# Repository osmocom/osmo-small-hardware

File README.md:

osmo-small-hardware - Various small Osmocom Hardware Projects
=============================================================

This repository contains a number of OSHW (open source hardware)
designs.  They are part of the [Osmocom](https://osmocom.org/) Open
Source Mobile Communications project.

Most of the designs are done in EAGLE CAD; the schematics and board
design files as well as the BOM are contained in this repository.

GIT Repository
--------------

You can clone from the official osmo-small-hardware repository using

	git clone https://gitea.osmocom.org/electronics/osmo-small-hardware

There is a web interface at <https://gitea.osmocom.org/electronics/osmo-small-hardware>

Contributing
------------

Our coding standards are described at
https://osmocom.org/projects/cellular-infrastructure/wiki/Coding_standards

We us a gerrit based patch submission/review process for managing
contributions.  Please see
https://osmocom.org/projects/cellular-infrastructure/wiki/Gerrit for
more details

clock-converter
---------------

The osmo-clock-conv is a small board for low-jitter conversion of a sine
clock into a square clock, based around the LTC6957-4.

* [Homapege](https://osmocom.org/projects/osmo-clock-conv)

clock-generator
---------------

Osmocom Clock Generator board, using the Si5351C clock synthesizer to
derive up to 8 different clocks from a single clock reference, such as a
10MHz GPS-DO or OCXO.

* [Homepage](https://osmocom.org/projects/osmo-clock-gen)

dus-lmt-breakout
----------------

This is a break-out board for the LMT port of Ericsson DUS-31/41
baseband units.

e1-tap
------

The Osmocom E1/T1 tap adapter allows you to tap into the communication
of an E1/T1 line.

* [Homepage](https://osmocom.org/projects/e1-tap)

eksos-rj45-breakout
-------------------

This contains a couple of break-out boards which can be used to break out the
ISDN / PSTN ports of a Nokia EKSOS V5 access network.

gtm900-breakout
---------------

Break-out board for the GTM900B Calypso based GSM cellular modem.

mpcie-breakout
--------------

This is a small break-out board for miniPCIe (mPCIe) type cellular /
WWAN modems.

* [Homepage](https://osmocom.org/projects/mpcie-breakout)

multivoltage-uart
-----------------

* [Homepage](https://osmocom.org/projects/mv-uart)

ngff-breakout
-------------

This is a small break-out board for M.2 (NGFF) type cellular / WWAN
modems.

* [Homepage](https://osmocom.org/projects/ngff-breakout)

ohm4-ocxo
---------

osmo-lea6t-gps
--------------

Small evaluation board for the u-blox LEA6-T timing GPS receiver.

osmo-nvs-gps
------------

Small evaluation board for the NVS GPS receiver.

rj45-jumper-box
---------------

A jumper box for RJ45 cables. Useful for the many different RS232
console pin-outs on RJ45.

* [Homepage](https://osmocom.org/projects/misc-hardware/wiki/RJ45_jumper_box)

rj45-switch
-----------

sc14dect-breakout
-----------------

Small evaluation board for the SC15 DECT module

sfp-breakout + sfp-experimenter
-------------------------------

Boards for playing with SFP transceivers

* [Homepage](https://osmocom.org/projects/misc-hardware/wiki/Sfp-breakout)

siu-clock-breakout
------------------

A break-out board for the clock/sync port on the Ericsson SIU-02

rbs6k-diy-rack
--------------

A DYI small rack for housing Ericsson RBS 6000 equipment like DUL + DUG + RUS made from wooden panels and a laser-cut back plate for fans.

fcd155-breakout
---------------

This is a small break-out board to adapt the RAD FCD-155 8xE1 high-density 44-pin D-SUB connector to 8xRJ45 in standard E1 pinout.

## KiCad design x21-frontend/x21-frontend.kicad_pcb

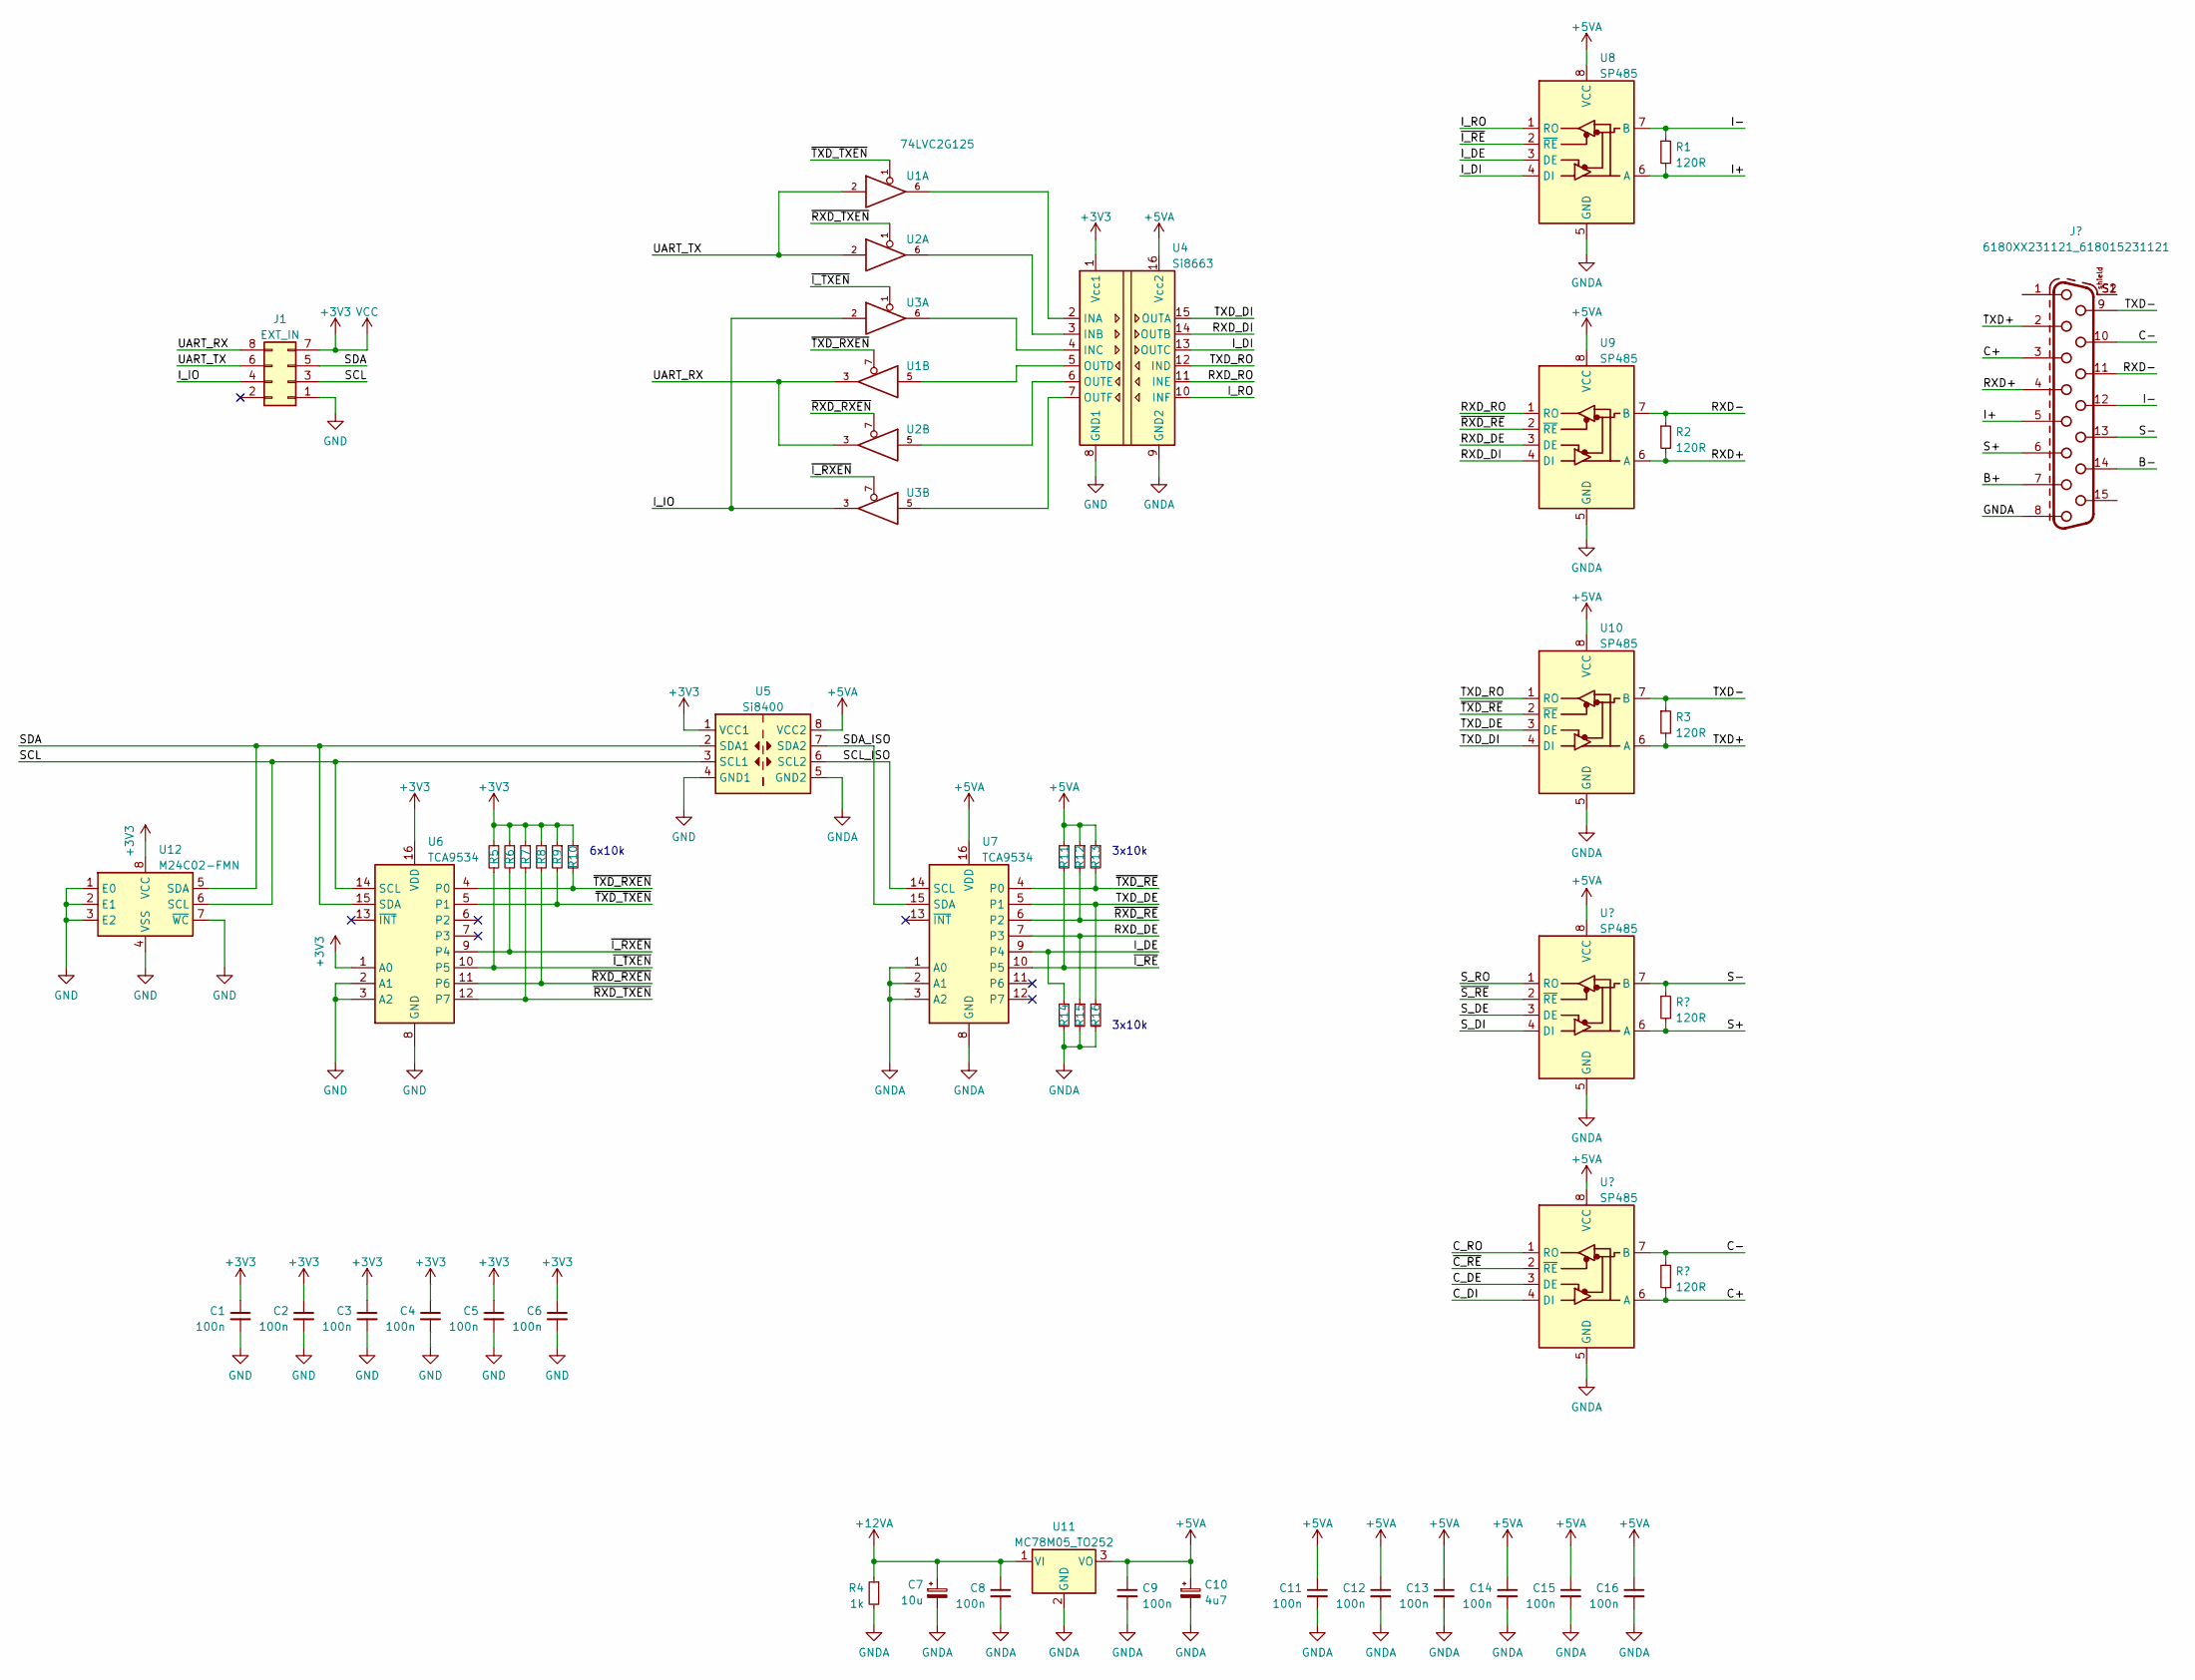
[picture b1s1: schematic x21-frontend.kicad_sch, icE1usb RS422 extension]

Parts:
C1, C2, C3, C4, C5, C6, C8, C9, C11, C12, C13, C14, C15, C16: 100n; C_0603_1608Metric
C7: 10u; CP_EIA-3216-18_Kemet-A
C10: 4u7; CP_EIA-3216-18_Kemet-A
J1: EXT_IN; PinSocket_2x04_P2.54mm_Vertical
R1, R2, R3: 120R; R_0603_1608Metric
R4: 1k; R_0603_1608Metric
R5, R6, R7, R8, R9, R10, R11, R12, R13, R14, R15, R16: 10k; R_0603_1608Metric
U1, U2, U3: 74LVC2G125; TSSOP-8_3x3mm_P0.65mm
U4: Si8663; SSOP-16_3.9x4.9mm_P0.635mm
U5: Si8400; SOIC-8_3.9x4.9mm_P1.27mm
U6, U7: TCA9534; SOIC-16W_7.5x10.3mm_P1.27mm
U8, U9, U10: SP485; SOIC-8_3.9x4.9mm_P1.27mm
U11: MC78M05_TO252; TO-252-2
U12: M24C02-FMN; SOIC-8_3.9x4.9mm_P1.27mm

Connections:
+3V3: C1.1, C2.1, C3.1, C4.1, C5.1, C6.1, J1.7, R5.1, R6.1, R7.1, R8.1, R9.1, R10.1, U1.8 (VCC), U2.8 (VCC), U3.8 (VCC), U4.1 (Vcc1), U5.1 (VCC1), U6.1 (A0), U6.16 (VDD), U12.8 (VCC)
+5VA: C9.1, C10.1, C11.1, C12.1, C13.1, C14.1, C15.1, C16.1, R11.1, R12.1, R13.1, U4.16 (Vcc2), U5.8 (VCC2), U7.16 (VDD), U8.8 (VCC), U9.8 (VCC), U10.8 (VCC), U11.3 (VO)
+12VA: C7.1, C8.1, R4.1, U11.1 (VI); also elsewhere on the board
/PPS+: R1.2, U8.6 (A); also elsewhere on the board
/PPS-: R1.1, U8.7 (B); also elsewhere on the board
/PPS_DE: R14.1, U7.9 (P4), U8.3 (DE)
/PPS_DI: U4.13 (OUTC), U8.4 (DI)
/PPS_IO: J1.4, U3.2, U3.3
/PPS_RO: U4.10 (INF), U8.1 (RO)
/RXD+: R2.2, U9.6 (A); also elsewhere on the board
/RXD-: R2.1, U9.7 (B); also elsewhere on the board
/RXD_DE: R15.1, U7.7 (P3), U9.3 (DE)
/RXD_DI: U4.14 (OUTB), U9.4 (DI)
/RXD_RO: U4.11 (INE), U9.1 (RO)
/SCL: J1.3, U5.3 (SCL1), U6.14 (SCL), U12.6 (SCL)
/SCL_ISO: U5.6 (SCL2), U7.14 (SCL)
/SDA: J1.5, U5.2 (SDA1), U6.15 (SDA), U12.5 (SDA)
/SDA_ISO: U5.7 (SDA2), U7.15 (SDA)
/TXD+: R3.2, U10.6 (A); also elsewhere on the board
/TXD-: R3.1, U10.7 (B); also elsewhere on the board
/TXD_DE: R16.1, U7.5 (P1), U10.3 (DE)
/TXD_DI: U4.15 (OUTA), U10.4 (DI)
/TXD_RO: U4.12 (IND), U10.1 (RO)
/UART_RX: J1.8, U1.3, U2.3
/UART_TX: J1.6, U1.2, U2.2
/~PPS_RE: R11.2, U7.10 (P5), U8.2 (~RE)
/~PPS_RXEN: R6.2, U3.7, U6.9 (P4)
/~PPS_TXEN: R5.2, U3.1, U6.10 (P5)
/~RXD_RE: R12.2, U7.6 (P2), U9.2 (~RE)
/~RXD_RXEN: R8.2, U2.7, U6.11 (P6)
/~RXD_TXEN: R7.2, U2.1, U6.12 (P7)
/~TXD_RE: R13.2, U7.4 (P0), U10.2 (~RE)
/~TXD_RXEN: R10.2, U1.7, U6.4 (P0)
/~TXD_TXEN: R9.2, U1.1, U6.5 (P1)
GND: C1.2, C2.2, C3.2, C4.2, C5.2, C6.2, J1.1, U1.4 (GND), U2.4 (GND), U3.4 (GND), U4.8 (GND1), U5.4 (GND1), U6.2 (A1), U6.3 (A2), U6.8 (GND), U12.1 (E0), U12.2 (E1), U12.3 (E2), U12.4 (VSS), U12.7 (~WC)
GNDA: C7.2, C8.2, C9.2, C10.2, C11.2, C12.2, C13.2, C14.2, C15.2, C16.2, R4.2, R14.2, R15.2, R16.2, U4.9 (GND2), U5.5 (GND2), U7.1 (A0), U7.2 (A1), U7.3 (A2), U7.8 (GND), U8.5 (GND), U9.5 (GND), U10.5 (GND), U11.2 (GND); also elsewhere on the board
unnamed: U1.5, U4.5 (OUTD)
unnamed: U1.6, U4.2 (INA)
unnamed: U2.5, U4.6 (OUTE)
unnamed: U2.6, U4.3 (INB)
unnamed: U3.5, U4.7 (OUTF)
unnamed: U3.6, U4.4 (INC)

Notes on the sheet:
6x10k
3x10k

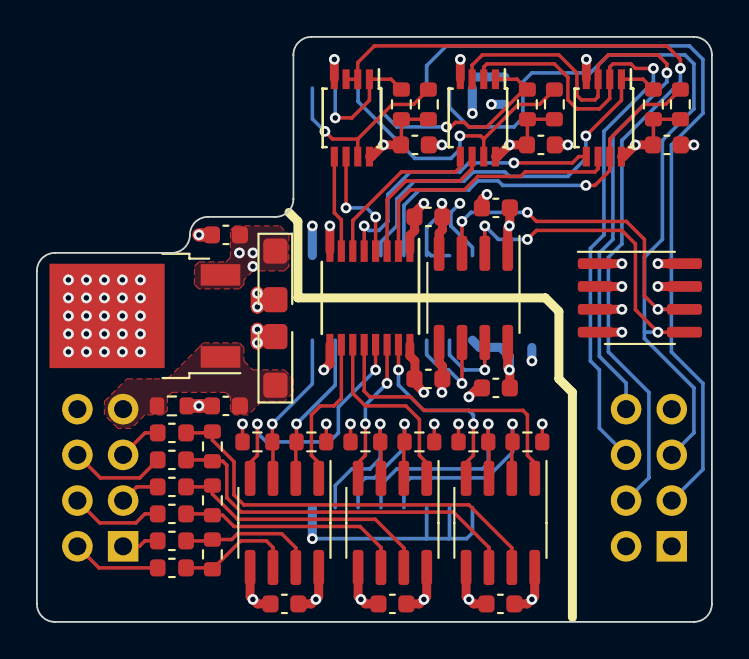
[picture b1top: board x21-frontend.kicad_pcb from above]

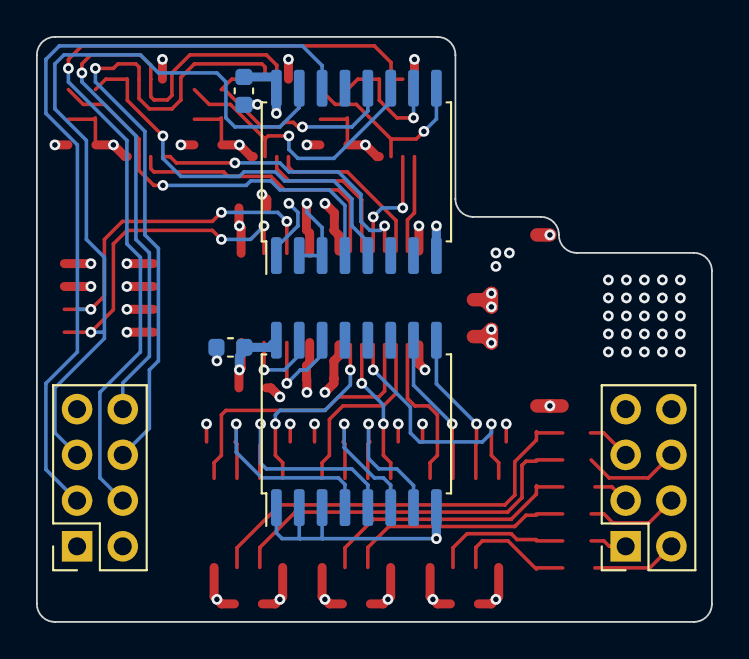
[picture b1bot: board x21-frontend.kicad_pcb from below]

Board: 4 copper layers, 37.5 x 32.5 mm, 52 parts (6 on the bottom side), 48 nets.

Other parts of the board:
F1, F2, F3, F4, F5, F6: 300mA; Fuse_0603_1608Metric
J2: EXT_OUT; PinSocket_2x04_P2.54mm_Vertical

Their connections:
+12VA: J2.7; also elsewhere on the board
/PPS+: F2.2; also elsewhere on the board
/PPS-: F1.1; also elsewhere on the board
/RXD+: F4.2; also elsewhere on the board
/RXD-: F3.1; also elsewhere on the board
/TXD+: F6.2; also elsewhere on the board
/TXD-: F5.1; also elsewhere on the board
GNDA: J2.8; also elsewhere on the board
unnamed: F1.2, J2.1
unnamed: F2.1, J2.2
unnamed: F3.2, J2.3
unnamed: F4.1, J2.4
unnamed: F5.2, J2.5
unnamed: F6.1, J2.6

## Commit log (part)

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2016-10-07 WIP: design for a multi-voltage USB UART
    * an adjustible LDO with rotary switch is able to configure the UART
    voltage levels as needed.
    * alternatively, the UART logic level voltage (in the 1.8-3.3V range)
    can be provided by an external voltage reference.
    * TVS diodes protect the USB and UART sides from overvoltage and ESD
    * all voltages are available on a header to supply external circuitry
2016-10-08 move all mv-uart files to sub-directory
2016-10-08 mpcie-breakout: add rendered gerber files
2016-10-08 mv-uart: use Seeed Studio DRU
2016-10-09 mv-uart: Add digikey link for all major parts
2016-10-09 mv-uart: Add PDF renderings
2016-10-10 add .gitignore
2016-10-27 mv-uart: Use SP6T flash *without* OFF position
2016-10-27 mpcie-breakout: Add series LED for LED_WWAN
2016-10-28 add PCB panel images for mv-uart and mpcie-breakout
2016-10-28 mv-uart: Add schematics + placement as PDF
2016-10-28 mpcie-breakoud: Add pdf renderings of schematics
2017-03-23 mpcie-breakout: Enlarge to 70x70mm, add SMA, U.FL and Mounting Holes
2017-03-23 mcie-breakout: Align bLabels, more vias, cosmetics
2017-03-23 mpcie-breakout: disable tPlace layer
2017-03-23 mpcie-breakout: Change to vertical SMA jacks
2017-03-23 mpcie-breakout: update BOM
2017-03-27 Add ngff-breakout as copy of mpcie-breakout
    ... ngff specific modifications will follow
2017-04-04 mpcie-breakout: update .mnt/.mnb files with v3 pcb
2017-05-07 import e1-tap design files
    This is a project started in 2012 to have an easy-to-use E1/T1 tap.
2017-07-22 mv-uart: annotate individual pins in brd and generate mv-uart-pinout.pdf
2018-06-07 sfp: add Eagle lib for SN65LVDS180 LVDS diff line xcvr
2018-06-19 sfp: add license to sch
2018-08-17 spf: revise both SFP designs (OSM#3313/OSM#3314)
2018-08-21 sfp: Use minimum clearance of 0.25mm as 0.15mm is needlessly tight in this board
2018-08-30 sfp: add part numbers for SFP conn and cage
2018-10-06 add SFP multi-source agreement to give context to the boards
2019-01-21 clock-generator: More work on schematics (USB, UART, ESD)
2019-01-26 clock-gen: Add SPI; UEXT header; mounting holes; do layout/routing
2019-01-27 clock-gen: finish routing of PCB layout
2019-01-27 clock-gen: Update gpio spreadsheet with all assignments
    The assignments have been chosen to be nearly identical to the
    SAMD11-XPRO board.
2019-02-14 clock-converter: Add attributes with digikey links
2019-05-08 sfp: update BOMs for both breakout and experimenter PCBs
2019-06-12 ngff-breakout: make 4layer PCB
2019-06-19 clock-generator: add tracking LDO, make PCB four layer
2019-06-19 clock-generator: compacting + place MTA100 header (solves OSM#4050)
2019-06-19 clock-generator: changes adressing OSM#4050
    A shouded UEXT would need much space; no room for an MTA100 yet... tbd
2019-06-22 add placement files for top and bottom
2019-06-22 add CAM file for generating gerber output
2019-06-22 update gerbers...
2019-06-22 add fiducials for automatic mounting of components
2019-06-22 component placement PDFs bottom and top
2019-06-22 don't put solder cream on SMA edge pads.
    The sma edge connectors are hand soldered after the SMT soldering
    is already done. We don't want to have solder paste on them...
2019-06-22 add updated PDF schematics
2019-06-22 initial import of osmo-nvs-gps project
    This is a small eval board for the NVS GPS/GLONASS/GALILEO module,
    exporting UARTs on headers.
2019-06-22 add gerber output of osm-nvs-gps v3
2019-06-22 final v3 as it goes in pcb production
    * smash components and move labels to where they can be read
    * add indication of + / GND to X3/X4
    * re-route some traces to ensure sufficient distance between them
    * make all traces 0.508 mm wide, even signal traces.
2019-06-22 v3 final with gerber output
2019-08-07 add SC14CVMDECT module breakout board
2019-08-27 ngff: finishing work
2019-09-17 ngff: set R9 to 100k (solves OS#4209)
2019-09-19 ngff: remove bogus packages names with '@1' by re-importing std lib
2019-09-24 ngff: repair one critical via for ERC passing
2019-09-25 ngff: add / refresh most ext'd attribs for eBOM
2019-10-17 ngff: connect pin 4 @X2 to GND (solves OS#4216)
2019-10-18 ngff: revert increased clearance for supply net class
    ...and instead change class membership of an affected wire.
2019-11-22 ngff-breakout: update BOM
2020-01-09 ngff: add product links to all one- and two-row 2,54mm pin header
2020-01-31 clock-gen: update ATSAMD21's BOM attributes (solves OS#4387)
2020-04-20 initial commit for a GTM900 breakout PCBA
    An additional mirrored FPC header will still be maintained
    as long as this PCBA is discussed/revised.
    This is going to be a OSHW CC-BY-SA.
2020-05-18 gtm900-bo: routing done, no airwires left, mirrored FPC removed
2020-05-19 gtm900-bo: re-introduce serial 0R on UART_RI
    ...not, that it was needed, but just in case...
2020-05-27 gtm900-bo: complete v1 eBOM + export as gnumeric and xls format
2020-06-04 gtm900-bo: exchange main LDO's BOM attributes
    Although the correct name was given in the schematic (MCP1827T-ADJE/ET),
    the BOM contained an LD1085, which is part of the same library...
    Now the extended attributes also reflect the correct part.
2020-06-08 clock-generator: update schematics pdf
2020-07-07 clock-generator: upd ext'd BOM attributes and update v2 eBOM
2020-07-17 add SIU clock breakout board design
    This board contains a 10P10C connector in the same pin-out as the
    Ericsson SIU-02 together with some differential receivers/drivers to
    convert the 1PPS from/to single-ended signals.
2020-07-27 siu-clock-breakout: Add missing component values
2020-09-10 mpcie-breakout: Remove GND via underneath U.FL connectors
2020-10-09 siu-clock-breakout: Add actual fischer TFP 4 outline
2020-10-09 clock-generator-frontpanel: Fix spacing of panel mount cut-outs
    they must not be symmetric, but in multiple of 5.08mm
2020-10-14 add export DXF for production (mirrored)
2020-11-01 initial design for DUS LMT breakout board
2021-01-11 ngff-breakout: add BOM attributes for 2.45mm stand-off and M.2 conn
2021-01-29 ngff-breakout: improve GND around 4th MHF4-SMA section
2021-03-21 add README.md on what this repository is all about
2021-03-30 README.md fix urls for cloning and cgit
2021-04-23 ngff-cardem: start design
2021-04-24 ngff-cardem: better function groups' placement
2021-04-26 ngff-cardem: remove SIM switch trio and connect straight to pivot
    This way the close-pivot OE is the only which needs a pull-down.
    Seven FET switches remain for other uses, four of them in a now
    usused seperate OE group.
2021-05-19 ngff-cardem: state w/ changes as of 18th May
2021-06-03 ngff-cardem: reduce number of options jumper to 3
2021-06-04 ngff-cardem: add SIM Vcc switch logic
    ... consisting of two FPF2109 and a Schottky diode. Needs two GPIOs,
    PU and PD for default "modem gives SIM pwr".
2021-06-04 ngff-cardem: bring /FLAG of IC1 to a GPIO (solves SYS#5477)
    GPIO is PA8 (former QMOD's 'SIMPRES2').
    Note, that the OCP of the FPF2109 is 200mA; there is no 100mA version
    in this series and w/ 1V8 lowest Vin.
2021-06-06 ngff-cardem: 4-position jumper conn instead 3 pos. w/ NGFF_RESET exposed
    ... on an OC inverter
2021-06-09 ngff-cardem: connect both SIMTRACE LEDs and assign to GPIOs
    ... like in the QuadModem for the first slot, the secont one like
    in the Simtrace
    adresses: SYS#5472
2021-06-10 ngff-cardem: update from 'rc-sysmocom.lbr' to purge footprints w/ "..@1"
2021-06-11 ngff-cardem: length matching for USB3
2021-06-13 ngff-cardem: add proper floppy power conn w/ a 2-resistor solder switch
2021-06-13 ngff-cardem: examine ERC + DRC for new part
2021-06-13 ngff-cardem: run renumber-sheet.uld and normalize-texts2.ulp
2021-07-05 add ncn8025-brekaout board
    This is a small eval/breakout board for the NCN8025 smart card interface IC
2021-09-03 sfp-experimnter: update extd attribs on D1, D2 to avail types
2021-09-08 ngff-cardem: populate R102 to uncond' release /NGFF_RESET (solves SYS#5531)
2021-09-09 ngff-cardem: split C301 into two footprints (solves SYS#5614)
2021-09-09 ngff-cardem: adjust setting resistors for Murata OKL (solves SYS#5613)
2021-09-22 ngff-cardem: improve clearance details to gain lower tech class than 8
    ... at Eurocircuits
2021-09-24 ngff-cardem: correct typo and add silk screen in bott name plate
2021-12-23 Add bgt-pwr-dist; A 3U component-carrier DC distribution module
2021-12-23 Add component carrier module mechanics for Ettus USRP B2xx
2022-01-31 bgt-pwr-dist: Finalize v2
    * no milling for DC jack (cheaper PCB production)
    * update version to v2
2022-02-14 bgt-pwr-dist: Increase restring on bottom side
    (v2 only increased it on top side, my mistake)
    Incremental fix for 84166fd4abd70575491d5e001d1fde690e2611e7
2022-03-24 ngff-cardem: Add PDF renderings of schematics + component placement
2022-05-13 xhfc-breakout: Data sheets of transformer and BAV99 diode
2022-05-13 xhfc-breakout: Complete line interface from chip to RJ45
2022-05-13 xhfc-breakout: bom attributes
2022-06-04 xhfc-breaout: Conncet SPI_INV to GND
    This was missing from the v1 design. SPI_INV must be tied to either high
    or low to select the SPI clock polarity. It was tied to low by manawyrm
    in his manual rework, so let's reflect this in the design accordingly.
2022-09-19 ngff-cardem: connect OsmoSer's GND to GND (solves SYS#5514)
    This change somehow didn't make it upstream though committed as
    bf211d3; so recreated.
2022-10-22 initial check-in of bgt-keystone project
    This adds a 3U component carrier module into which you can mix and
    match keystone modules as needed.
2023-01-20 rj45_jumper_box: Use different RJ45 jack; both on top layer
    The original design (one RJ45 on top, one on bottom) was easy to route
    but was difficult to handle. Let's swap both connectors to top, and use
    a low-cost Chinese RJ45.
2023-02-03 initial version of bgt-gs305e: BGT Mount for Netgear GS305E switch
2023-02-12 New design: plutosdr-revb-extclk
    This is a small circuit board containing the "external clock ref input"
    circuitry that was added to PlutoSDR RevD. It can be used to
    upgrade/rework RevB boards with the same clock input as the later RevD.
    Related: OS#5892
2023-04-14 sfp-*: change all 10µF/16V 0805 to 1206 (solves SYS#5397)
    also update all URLs to the current Digikey URI scheme
2023-05-15 sfp-experimenter: insert main fiducials
2023-07-02 plutosdr-revb-extclk: don't shut-down LTC via SD1/SD2
    In the original PlutoSDR RevC or higher, there's a BSS138 FET
    that [optionally] pulls low the SD1/SD2 pins in order to activate
    the external clock input.
    In this circuit, we don't have GPIO control but permanently enable
    the LTC.
    Related: OS#5892
2023-08-11 RJ45 breakout board for NOKA EKSOS ISDN / POTS ports
    These board designs assumes that you use a 64pos (type 3 a+c)
    DIN-connector with a flat ribbon cable to a 2x32 2.54mm pitch (IDE/SCSI
    style) header to interconnect them.
    The point is that assembling that ribbon cable with IDC technology is
    much faster than performing soldering or LSA+ type termination on 32
    individual wires.
2023-08-11 eksos-rj45-breakout16: ad label/copyright/license/OSHW
2023-08-11 README.md: Add note about EKSOS breakout boards
2023-08-21 amr-breakout: Add pull-ups for !AC97_RESET and !PRIMARY_DN
    Closes: OS#5369
2023-10-10 gtm900-breakout: add next design v3
2023-11-02 gtm900-bo: rename main files w/o explicit version
2023-11-06 gtm900-bo: add 47R into both UARTs' wires
2023-11-15 gtm900-bo: update v3 schema pdf
2024-01-18 gtm900-bo: change silkscreen name to 'OsmoGTM900 breakout v3'
2024-02-27 gtm900-bo: new SIM holder, add LCSC part numbers
    Now using a XunPu SIM-105B-ARP8 SIM holder which is somewhat close
    to the JAE SF7W008S1A.
2024-03-21 gtm900-bo: replace JLCPCB cpl file
    The missing T1,T2 now are in.
2024-05-08 ngff-cardem: update schema pdf
2024-10-26 rbs6k-dyi-rack: add rbs6k diy rack top/bottom panel drawing
2024-10-26 rbs6k-diy-rack: Add CC-BY-SA COPYING file
2024-10-26 rbs6k-dyi-rack: rbs6k_fan-hood_*.dxf - add centerlines to help layer, add marking layer for drillholes (only markings, no holes)
2024-10-26 rbs6k-dyi-rack: add first sketch for a hood to add fans to the 8U rbs6k frames
    no rounded corners yet
2024-10-26 rbs6k-dyi-rack: diy-rack: MeanWell RSP-750 power supply drawing
2024-11-17 GTM900: Add missing bottom solder mask layer
2024-12-04 Add a small break-out board for the FCD-155 8xE1 DB44 connector
2025-01-02 fcd-155-breakout: Fix pin-out for even numbered ports
    Related: OS#6678
